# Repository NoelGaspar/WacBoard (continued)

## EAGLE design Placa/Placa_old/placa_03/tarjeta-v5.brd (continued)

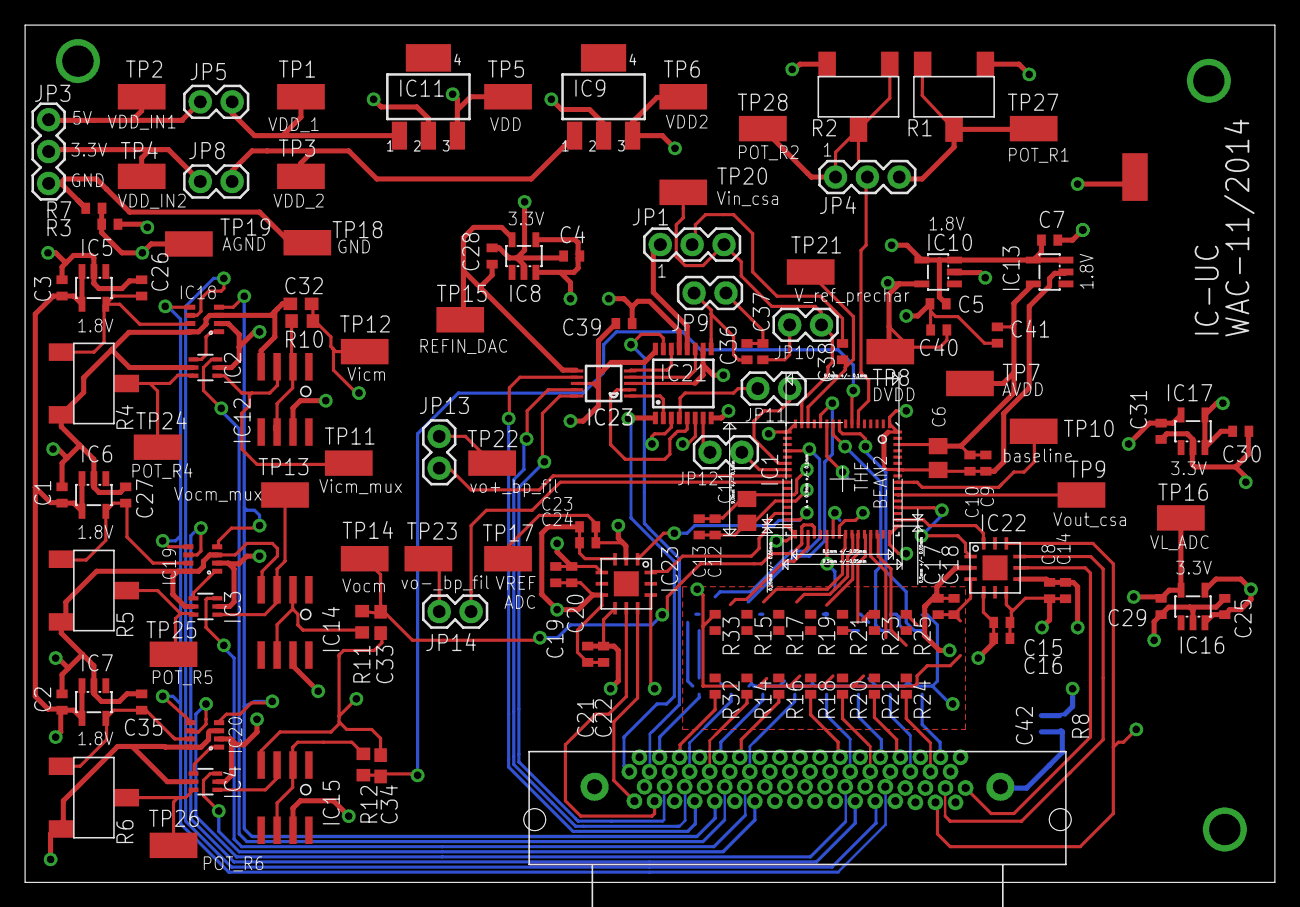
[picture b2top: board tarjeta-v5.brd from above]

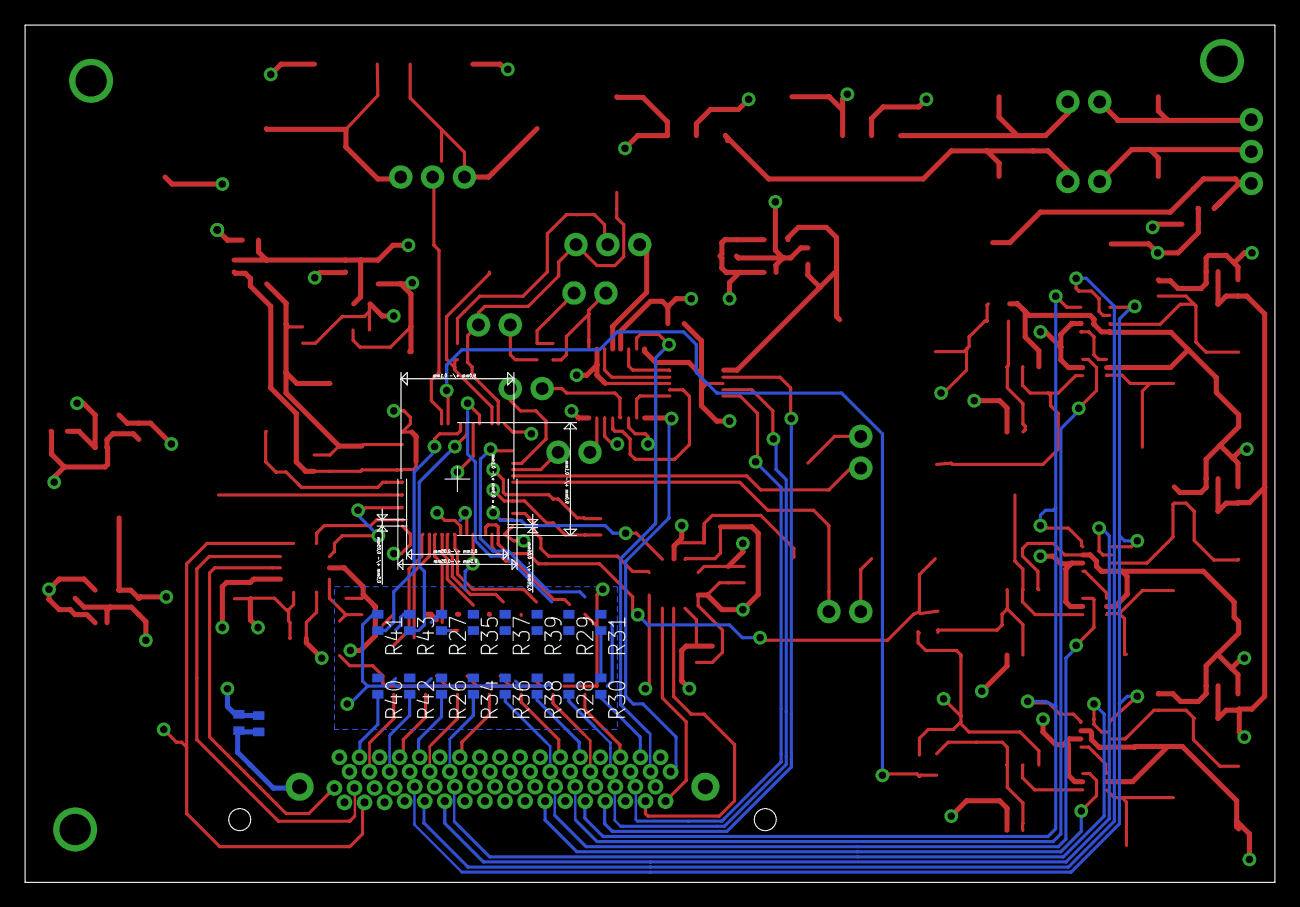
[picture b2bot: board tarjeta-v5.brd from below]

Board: 4 copper layers, 99.6 x 68.4 mm, 148 parts (18 on the bottom side), 111 nets.

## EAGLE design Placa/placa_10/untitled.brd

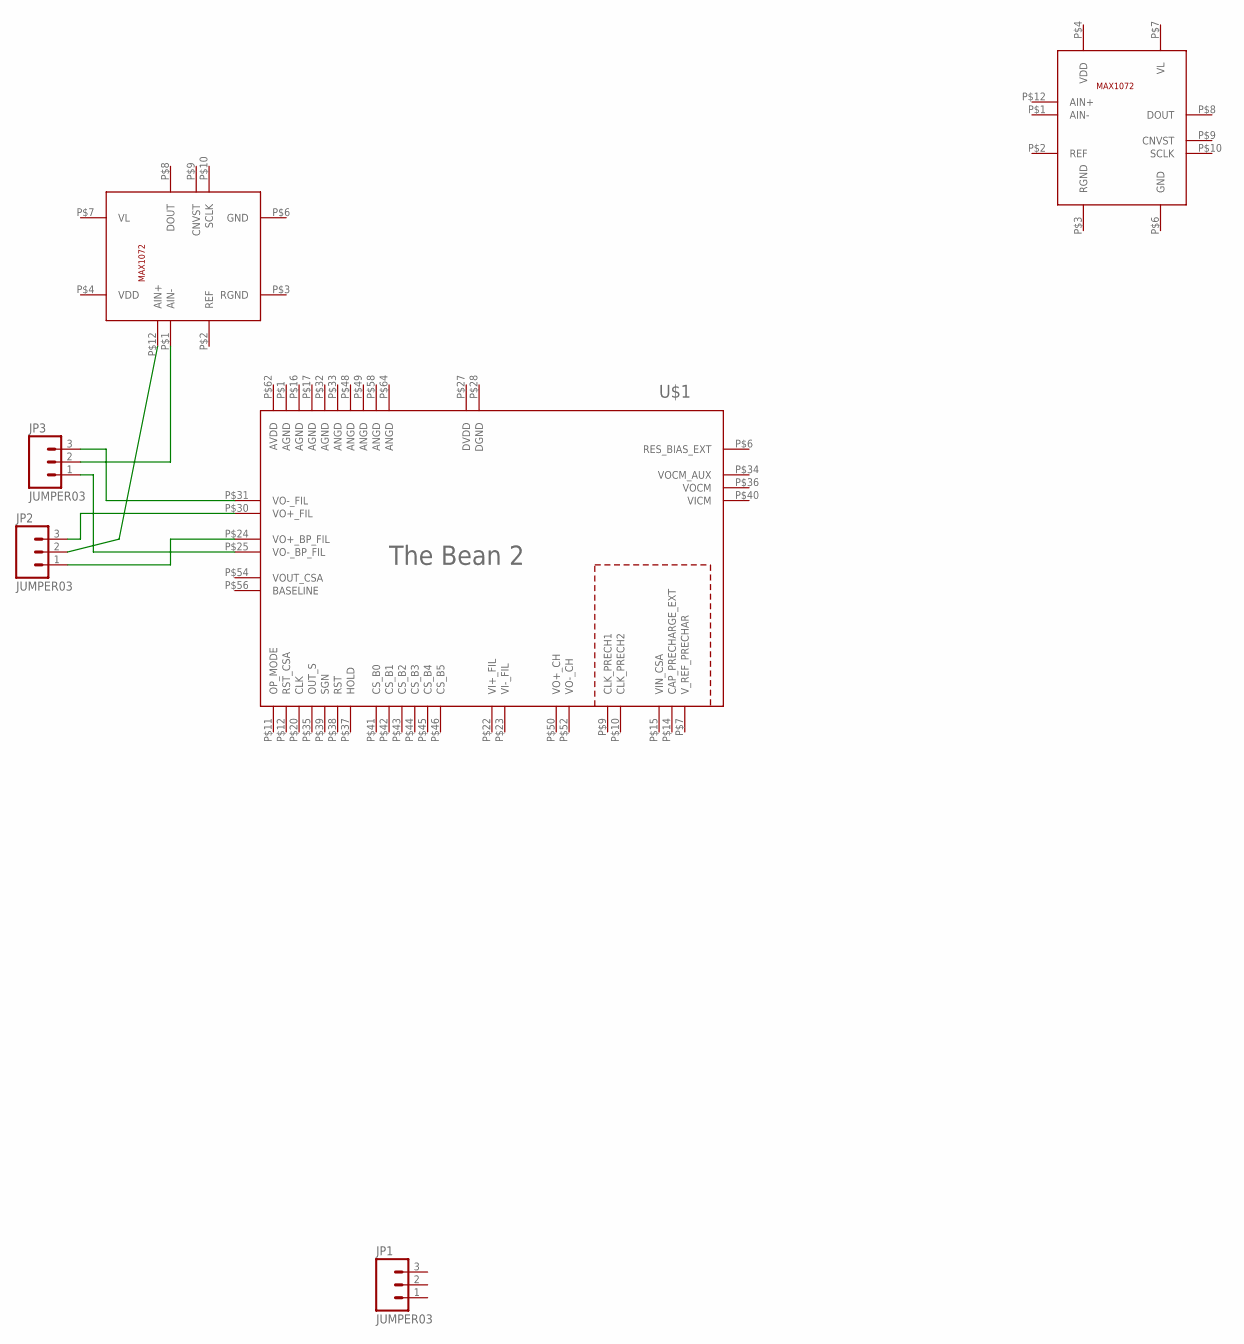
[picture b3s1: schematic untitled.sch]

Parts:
JP1, JP2, JP3: JUMPER03; 1X03
U$1: THEBEAN2; CQFP64
U$2, U$3: MAX1072; TQFN12

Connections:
AGND: U$1.P$1 (AGND), U$1.P$16 (AGND), U$1.P$17 (AGND), U$1.P$32 (AGND)
ANGD: U$1.P$33 (ANGD), U$1.P$48 (ANGD), U$1.P$49 (ANGD), U$1.P$58 (ANGD), U$1.P$64 (ANGD)
AVDD: U$1.P$62 (AVDD)
DGND: U$1.P$28 (DGND)
DVDD: U$1.P$27 (DVDD)
unnamed: JP3.3, U$1.P$31 (VO-_FIL)
unnamed: JP3.1, U$1.P$25 (VO-_BP_FIL)
unnamed: JP2.3, U$1.P$30 (VO+_FIL)
unnamed: JP2.1, U$1.P$24 (VO+_BP_FIL)
unnamed: JP3.2, U$2.P$1 (AIN-)
unnamed: JP2.2, U$2.P$12 (AIN+)

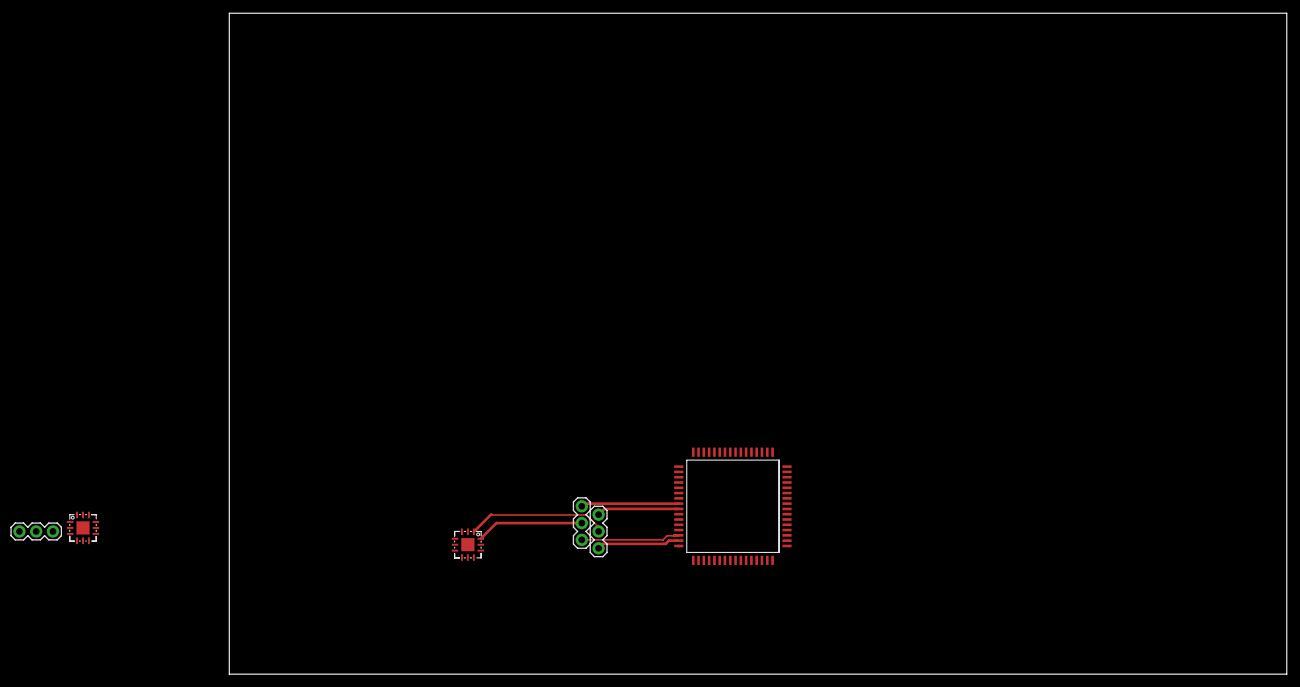
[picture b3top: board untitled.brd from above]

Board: 4 copper layers, 160.0 x 100.0 mm, 6 parts (0 on the bottom side), 8 nets.

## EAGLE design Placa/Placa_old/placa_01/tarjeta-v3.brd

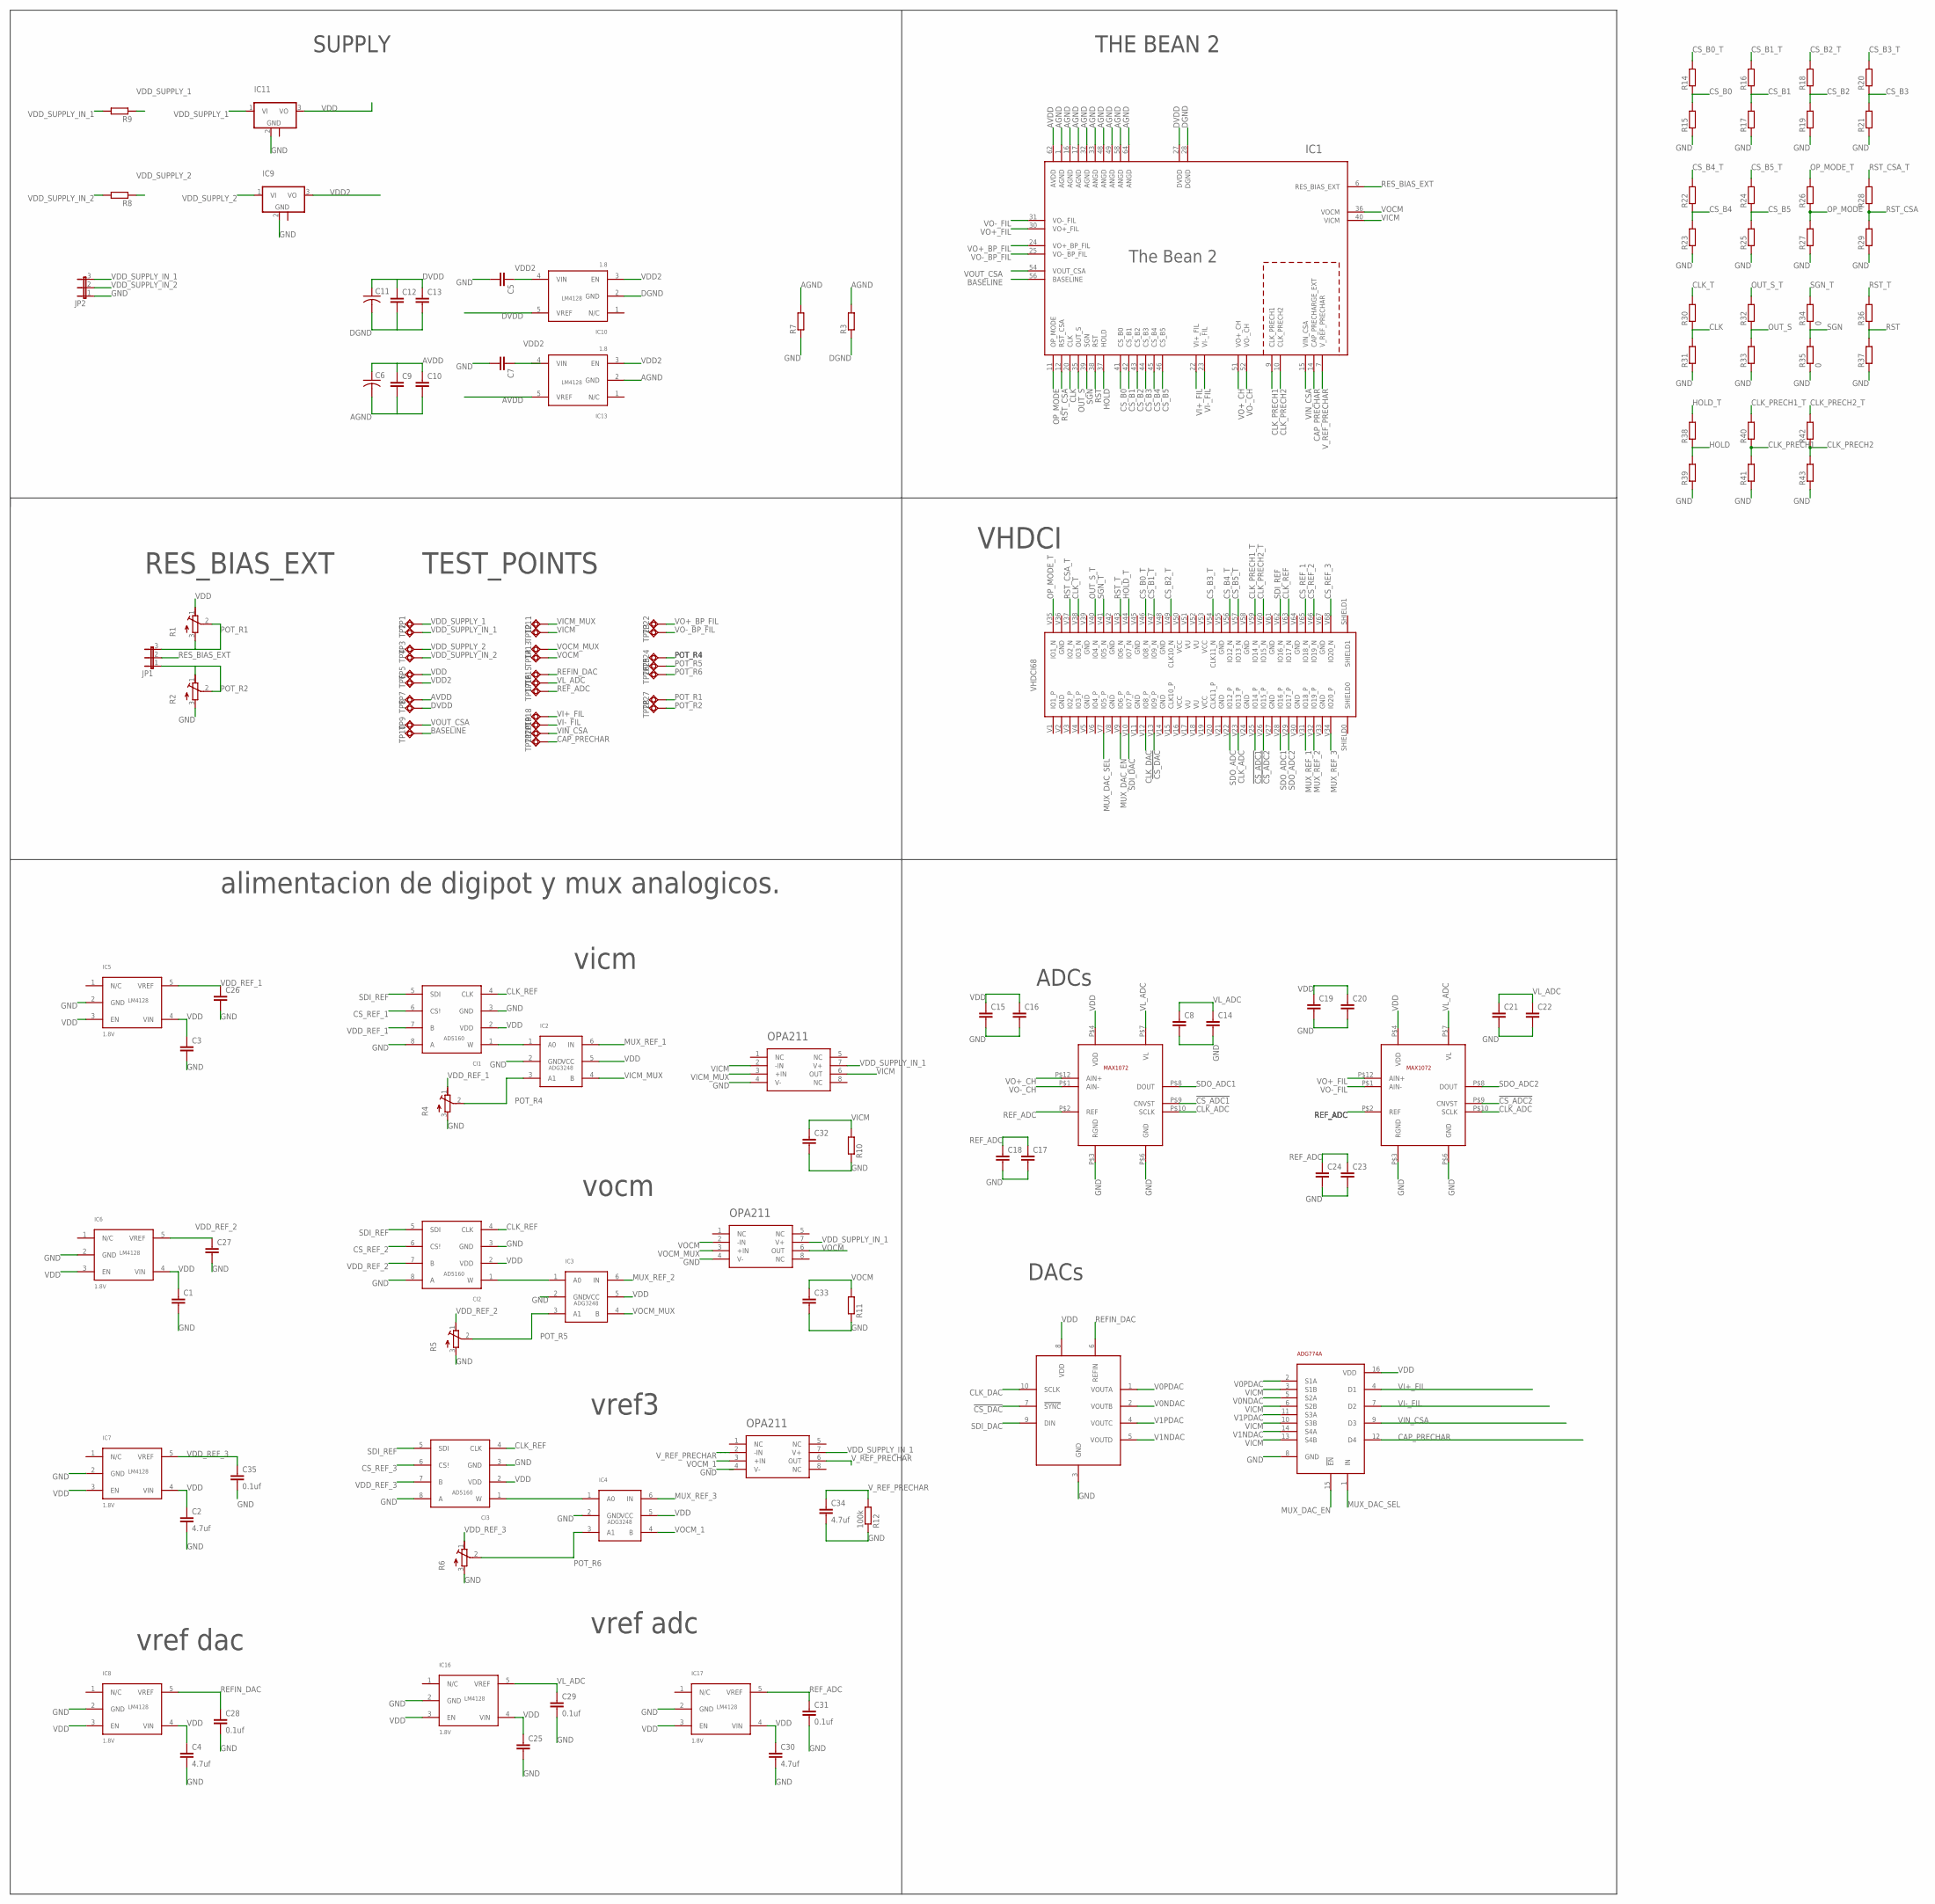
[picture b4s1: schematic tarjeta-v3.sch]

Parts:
C1, C3, C5, C7, C8, C9, C10, C12, C13, C14, C15, C16, C17, C18, C19, C20, C21, C22, C23, C24, C25, C26, C27, C32, C33: C-EUC0402; C0402
C2, C4, C30, C34: 4.7uf; C0402
C6, C11: C-USC0805; C0805
C28, C29, C31, C35: 0.1uf; C0402
CI1, CI2, CI3: AD5160; SOT23-8
IC1: THE_BEAN_2; QFN64
IC2, IC3, IC4: ADG3248; SC70
IC5, IC6, IC7, IC8, IC16, IC17: 1.8V; SOT23-5L
IC9, IC11: UA78M33DCY; SOT223
IC10, IC13: 1.8; SOT23-5L
IC12, IC14, IC15: OPA211; SOIC8
JP1, JP2: JP2E; JP2
R1, R2, R4, R5, R6: TRIMMER_ST5; ST-5EW
R3, R7, R8, R9, R10, R11, R14, R15, R16, R17, R18, R19, R20, R21, R22, R23, R24, R25, R26, R27, R28, R29, R30, R31, R32, R33, R36, R37, R38, R39, R40, R41, R42, R43: R-EU_R0402; R0402
R12: 100k; R0402
R34, R35: 0; R0402
TP1, TP2, TP3, TP4, TP5, TP6, TP7, TP8, TP9, TP10, TP11, TP12, TP13, TP14, TP15, TP16, TP17, TP18, TP19, TP20, TP21, TP22, TP23, TP24, TP25, TP26, TP27, TP28: TEST_POINT; TP
U$1: ADG774A; QSOP16
U$2: VHDCI68
U$3, U$5: MAX1072; TQFN12
U$4: DAC7554; MSOP10

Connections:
!CS_ADC1: U$2.V25 (IO14_P), U$3.P$9 (CNVST)
!CS_ADC2: U$2.V26 (IO15_P), U$5.P$9 (CNVST)
!CS_DAC: U$2.V13 (IO9_P), U$4.7 (!SYNC)
AGND: C6.2, C9.2, C10.2, IC1.1 (AGND), IC1.16 (AGND), IC1.17 (AGND), IC1.32 (AGND), IC1.33 (ANGD), IC1.48 (ANGD), IC1.49 (ANGD), IC1.58 (ANGD), IC1.64 (ANGD), IC13.2 (GND), R3.2, R7.2
AVDD: C6.1, C9.1, C10.1, IC1.62 (AVDD), IC13.5 (VREF), TP7.TP
BASELINE: IC1.56 (BASELINE), TP10.TP
CAP_PRECHAR: IC1.14 (CAP_PRECHARGE_EXT), TP21.TP, U$1.12 (D4)
CLK: IC1.20 (CLK), R30.1, R31.2
CLK_ADC: U$2.V23 (IO13_P), U$3.P$10 (SCLK), U$5.P$10 (SCLK)
CLK_DAC: U$2.V12 (IO8_P), U$4.10 (SCLK)
CLK_PRECH1: IC1.9 (CLK_PRECH1), R40.1, R41.2
CLK_PRECH1_T: R40.2, U$2.V59 (IO14_N)
CLK_PRECH2: IC1.10 (CLK_PRECH2), R42.1, R43.2
CLK_PRECH2_T: R42.2, U$2.V60 (IO15_N)
CLK_REF: CI1.4 (CLK), CI2.4 (CLK), CI3.4 (CLK), U$2.V63 (IO17_N)
CLK_T: R30.2, U$2.V38 (IO3_N)
CS_B0: IC1.41 (CS_B0), R14.1, R15.2
CS_B0_T: R14.2, U$2.V46 (IO8_N)
CS_B1: IC1.42 (CS_B1), R16.1, R17.2
CS_B1_T: R16.2, U$2.V47 (IO9_N)
CS_B2: IC1.43 (CS_B2), R18.1, R19.2
CS_B2_T: R18.2, U$2.V49 (CLK10_N)
CS_B3: IC1.44 (CS_B3), R20.1, R21.2
CS_B3_T: R20.2, U$2.V54 (CLK11_N)
CS_B4: IC1.45 (CS_B4), R22.1, R23.2
CS_B4_T: R22.2, U$2.V56 (IO12_N)
CS_B5: IC1.46 (CS_B5), R24.1, R25.2
CS_B5_T: R24.2, U$2.V57 (IO13_N)
CS_REF_1: CI1.6 (CS!), U$2.V65 (IO18_N)
CS_REF_2: CI2.6 (CS!), U$2.V66 (IO19_N)
CS_REF_3: CI3.6 (CS!), U$2.V68 (IO20_N)
DGND: C11.2, C12.2, C13.2, IC1.28 (DGND), IC10.2 (GND), R3.1
DVDD: C11.1, C12.1, C13.1, IC1.27 (DVDD), IC10.5 (VREF), TP8.TP
GND: C1.2, C2.2, C3.2, C4.2, C5.2, C7.2, C8.2, C14.2, C15.2, C16.2, C17.2, C18.2, C19.2, C20.2, C21.2, C22.2, C23.2, C24.2, C25.2, C26.2, C27.2, C28.2, C29.2, C30.2, C31.2, C32.2, C33.2, C34.2, C35.2, CI1.3 (GND), CI1.8 (A), CI2.3 (GND), CI2.8 (A), CI3.3 (GND), CI3.8 (A), IC2.2 (GND), IC3.2 (GND), IC4.2 (GND), IC5.2 (GND), IC6.2 (GND), IC7.2 (GND), IC8.2 (GND), IC9.2 (GND), IC11.2 (GND), IC12.4 (V-), IC16.2 (GND), IC17.2 (GND), JP2.1, R2.3, R4.3, R5.3, R6.3, R7.1, R10.1, R11.1, R12.1, R15.1, R17.1, R19.1, R21.1, R23.1, R25.1, R27.1, R29.1, R31.1, R33.1, R35.1, R37.1, R39.1, R41.1, R43.1, U$1.8 (GND), U$3.P$3 (RGND), U$3.P$6 (GND), U$4.3 (GND), U$5.P$3 (RGND), U$5.P$6 (GND)
HOLD: IC1.37 (HOLD), R38.1, R39.2
HOLD_T: R38.2, U$2.V44 (IO7_N)
MUX_DAC_EN: U$1.15 (!EN), U$2.V9 (IO6_P)
MUX_DAC_SEL: U$1.1 (IN), U$2.V7 (IO5_P)
MUX_REF_1: IC2.6 (IN), U$2.V31 (IO18_P)
MUX_REF_2: IC3.6 (IN), U$2.V32 (IO19_P)
MUX_REF_3: IC4.6 (IN), U$2.V34 (IO20_P)
unnamed: CI3.1 (W), IC4.1 (A0)
unnamed: CI1.1 (W), IC2.1 (A0)
unnamed: CI2.1 (W), IC3.1 (A0)
OP_MODE: IC1.11 (OP_MODE), R26.1, R27.2
OP_MODE_T: R26.2, U$2.V35 (IO1_N)
OUT_S: IC1.35 (OUT_S), R32.1, R33.2
OUT_S_T: R32.2, U$2.V40 (IO4_N)
POT_R1: JP1.3, R1.2, R1.3, TP27.TP
POT_R2: JP1.1, R2.1, R2.2, TP28.TP
POT_R4: IC2.3 (A1), R4.2, TP24.TP
POT_R5: IC3.3 (A1), R5.2, TP25.TP
POT_R6: IC4.3 (A1), R6.2, TP26.TP
REFIN_DAC: IC8.5 (VREF), TP15.TP, U$4.6 (REFIN)
REF_ADC: C17.1, C18.1, C23.1, C24.1, C31.1, IC17.5 (VREF), TP17.TP, U$3.P$2 (REF), U$5.P$2 (REF)
RES_BIAS_EXT: IC1.6 (RES_BIAS_EXT), JP1.2
RST: IC1.38 (RST), R36.1, R37.2
RST_CSA: IC1.12 (RST_CSA), R28.1, R29.2
RST_CSA_T: R28.2, U$2.V37 (IO2_N)
RST_T: R36.2, U$2.V43 (IO6_N)
SDI_DAC: U$2.V10 (IO7_P), U$4.9 (DIN)
SDI_REF: CI1.5 (SDI), CI2.5 (SDI), CI3.5 (SDI), U$2.V62 (IO16_N)
SDO_ADC: U$2.V22 (IO12_P)
SDO_ADC1: U$2.V28 (IO16_P), U$3.P$8 (DOUT)
SDO_ADC2: U$2.V29 (IO17_P), U$5.P$8 (DOUT)
SGN: IC1.39 (SGN), R34.1, R35.2
SGN_T: R34.2, U$2.V41 (IO5_N)
V0NDAC: U$1.5 (S2A), U$4.2 (VOUTB)
V0PDAC: U$1.2 (S1A), U$4.1 (VOUTA)
V1NDAC: U$1.14 (S4A), U$4.5 (VOUTD)
V1PDAC: U$1.11 (S3A), U$4.4 (VOUTC)
VCC: U$2.V16 (VCC), U$2.V19 (VCC), U$2.V50 (VCC), U$2.V53 (VCC)
VDD: C1.1, C2.1, C3.1, C4.1, C15.1, C16.1, C19.1, C20.1, C25.1, C30.1, CI1.2 (VDD), CI2.2 (VDD), CI3.2 (VDD), IC2.5 (VCC), IC3.5 (VCC), IC4.5 (VCC), IC5.3 (EN), IC5.4 (VIN), IC6.3 (EN), IC6.4 (VIN), IC7.3 (EN), IC7.4 (VIN), IC8.3 (EN), IC8.4 (VIN), IC11.3 (VO), IC16.3 (EN), IC16.4 (VIN), IC17.3 (EN), IC17.4 (VIN), R1.1, TP5.TP, U$1.16 (VDD), U$3.P$4 (VDD), U$4.8 (VDD), U$5.P$4 (VDD)
VDD1: C28.1
VDD2: C5.1, C7.1, IC9.3 (VO), IC10.3 (EN), IC10.4 (VIN), IC13.3 (EN), IC13.4 (VIN), TP6.TP
VDD_REF_1: C26.1, CI1.7 (B), IC5.5 (VREF), R4.1
VDD_REF_2: C27.1, CI2.7 (B), IC6.5 (VREF), R5.1
VDD_REF_3: C35.1, CI3.7 (B), IC7.5 (VREF), R6.1
VDD_SUPPLY_1: IC11.1 (VI), R9.1, TP1.TP
VDD_SUPPLY_2: IC9.1 (VI), R8.1, TP3.TP
VDD_SUPPLY_IN_1: IC12.7 (V+), IC14.7 (V+), IC15.7 (V+), JP2.3, R9.2, TP2.TP
VDD_SUPPLY_IN_2: JP2.2, R8.2, TP4.TP
VI+_FIL: IC1.22 (VI+_FIL), TP18.TP, U$1.4 (D1)
VI-_FIL: IC1.23 (VI-_FIL), TP19.TP, U$1.7 (D2)
VICM: C32.1, IC1.40 (VICM), IC12.2 (-IN), IC12.6 (OUT), R10.2, TP12.TP, U$1.3 (S1B), U$1.6 (S2B), U$1.10 (S3B), U$1.13 (S4B)
VICM_MUX: IC2.4 (B), IC12.3 (+IN), TP11.TP
VIN_CSA: IC1.15 (VIN_CSA), TP20.TP, U$1.9 (D3)
VL_ADC: C8.1, C14.1, C21.1, C22.1, C29.1, IC16.5 (VREF), TP16.TP, U$3.P$7 (VL), U$5.P$7 (VL)
VO+_BP_FIL: IC1.24 (VO+_BP_FIL), TP22.TP
VO+_CH: IC1.51 (VO+_CH), U$3.P$12 (AIN+)
VO+_FIL: IC1.30 (VO+_FIL), U$5.P$12 (AIN+)
VO-_BP_FIL: IC1.25 (VO-_BP_FIL), TP23.TP
VO-_CH: IC1.52 (VO-_CH), U$3.P$1 (AIN-)
VO-_FIL: IC1.31 (VO-_FIL), U$5.P$1 (AIN-)
VOCM: C33.1, IC1.36 (VOCM), IC14.2 (-IN), IC14.6 (OUT), R11.2, TP14.TP
VOCM_1: IC4.4 (B), IC15.3 (+IN)
VOCM_MUX: IC3.4 (B), IC14.3 (+IN), TP13.TP
VOUT_CSA: IC1.54 (VOUT_CSA), TP9.TP
VU: U$2.V17 (VU), U$2.V18 (VU), U$2.V51 (VU), U$2.V52 (VU)
V_REF_PRECHAR: C34.1, IC1.7 (V_REF_PRECHAR), IC15.2 (-IN), IC15.6 (OUT), R12.2

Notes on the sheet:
vicm
vocm
alimentacion de digipot y mux analogicos.
VHDCI
RES_BIAS_EXT
ADCs
SUPPLY
THE BEAN 2
DACs
TEST_POINTS
vref3
vref adc
vref dac

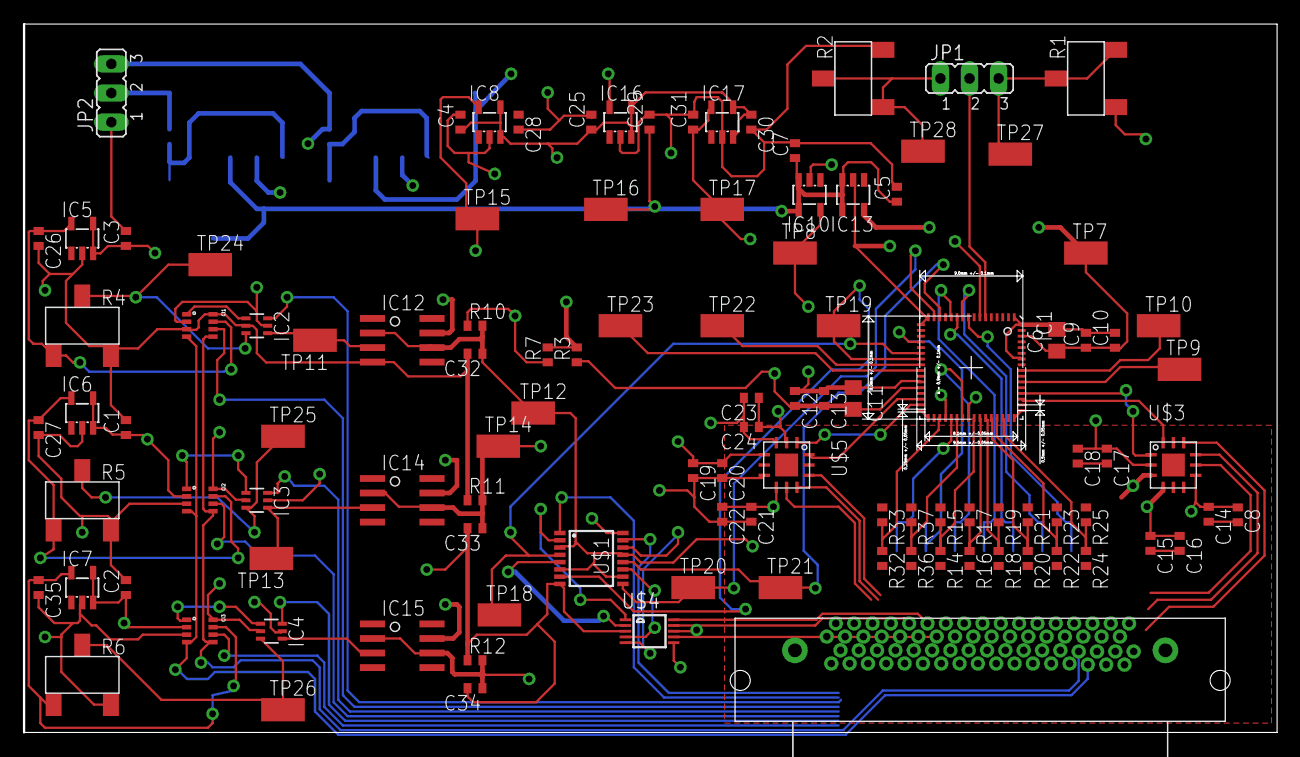
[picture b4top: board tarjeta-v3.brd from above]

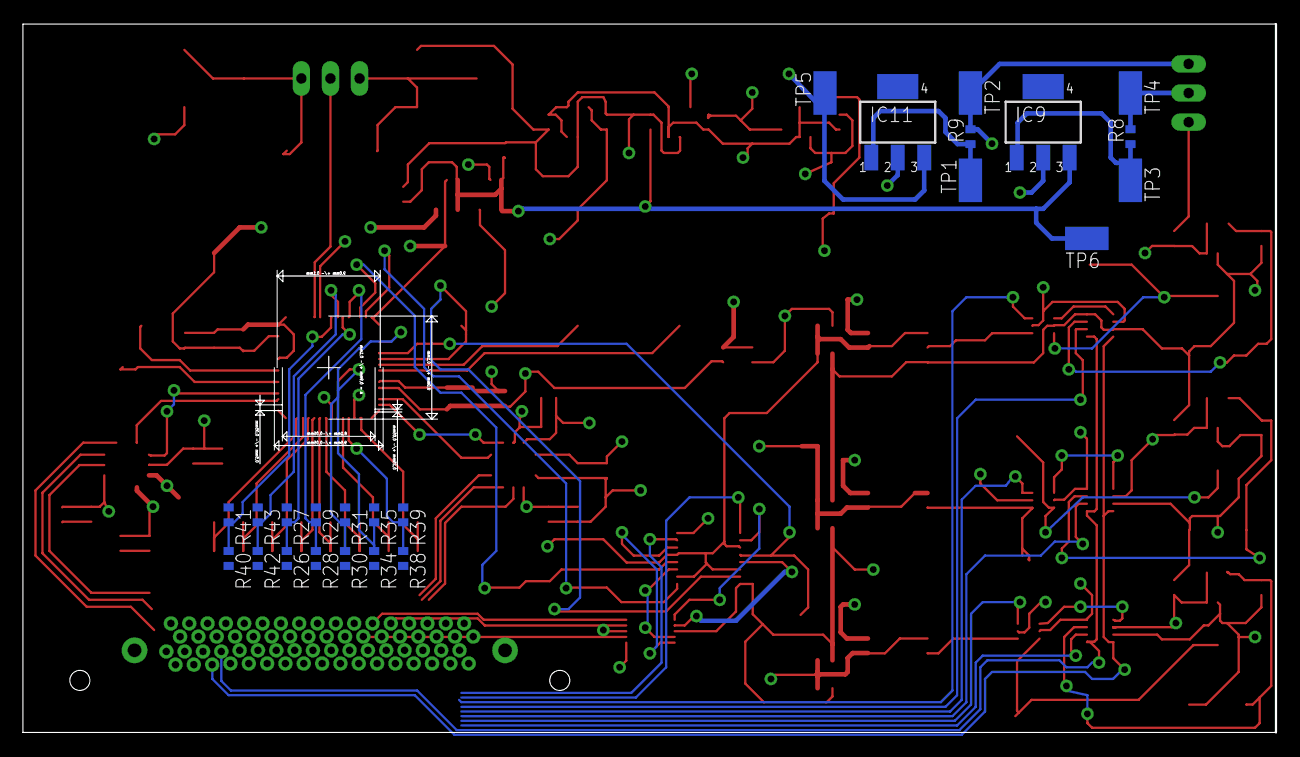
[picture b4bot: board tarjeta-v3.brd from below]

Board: 4 copper layers, 109.4 x 61.8 mm, 132 parts (24 on the bottom side), 98 nets.
